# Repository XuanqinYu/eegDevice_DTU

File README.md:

# eegDevice_DTU

Codes contains Python script to use, and codes in Arduino or ESP-IDF for developing.

Design files contains schematic design and PCB design in KiCAD. And the simulation circuit is done in Ti-Tina.

Manual introduces how to use the script to visualize data and develop the device.

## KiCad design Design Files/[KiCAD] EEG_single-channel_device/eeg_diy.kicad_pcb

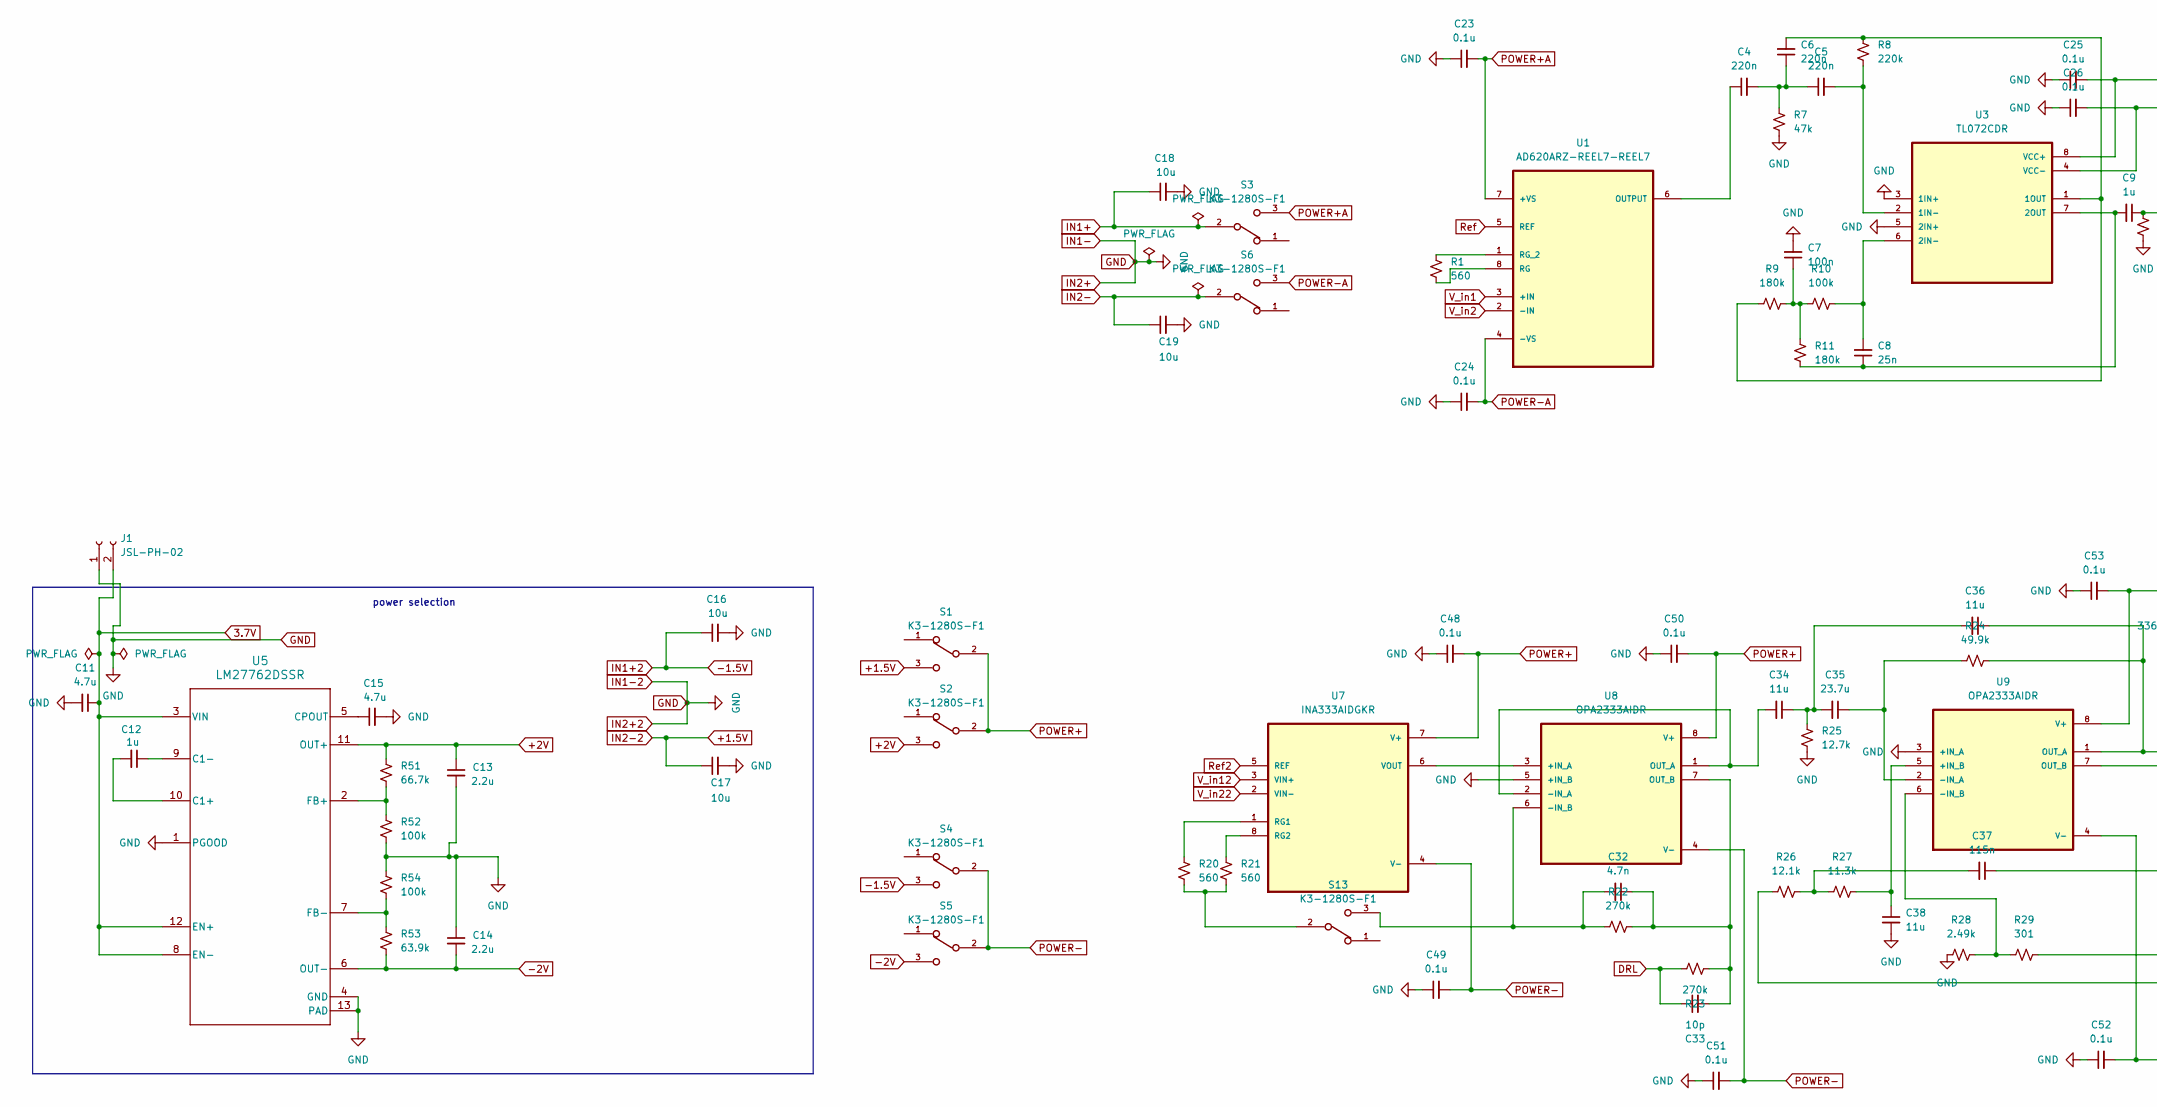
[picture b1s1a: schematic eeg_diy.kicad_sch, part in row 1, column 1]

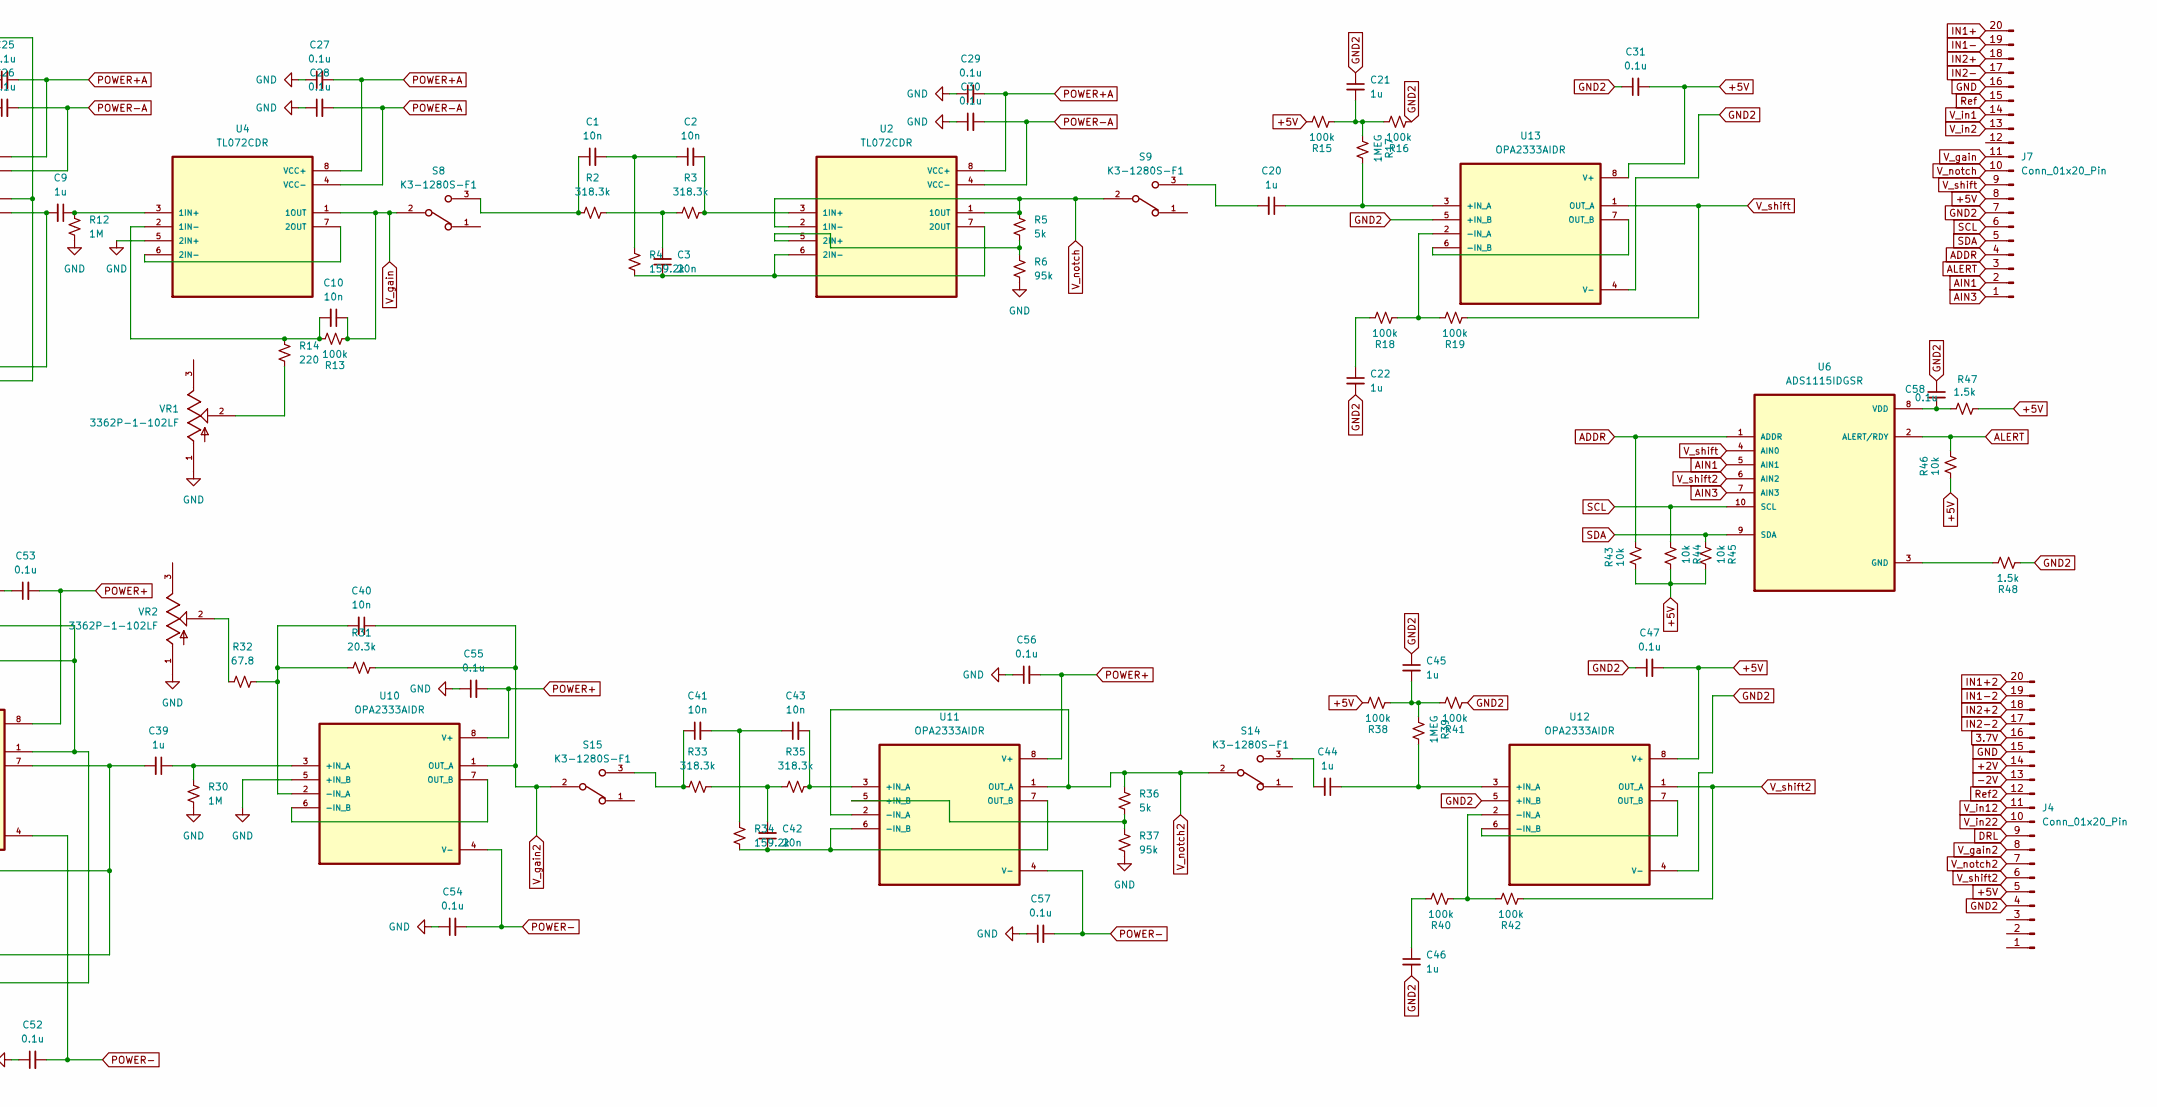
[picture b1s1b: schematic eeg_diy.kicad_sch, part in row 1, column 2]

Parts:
C1, C2, C10, C40, C41, C43: 10n; C_0805_2012Metric
C3, C42: 20n; C_0805_2012Metric
C4, C5, C6: 220n; C_0805_2012Metric
C7: 100n; C_0805_2012Metric
C8: 25n; C_0805_2012Metric
C9, C12, C20, C21, C22, C39, C44, C45, C46: 1u; C_0805_2012Metric
C11, C15: 4.7u; C_0805_2012Metric
C13, C14: 2.2u; C_0603_1608Metric
C16, C17, C18, C19: 10u; C_0805_2012Metric
C23, C24, C25, C26, C27, C28, C29, C30, C31, C47, C48, C49, C50, C51, C52, C53, C54, C55, C56, C57, C58: 0.1u; C_0805_2012Metric
C32: 4.7n; C_0805_2012Metric
C33: 10p; C_0603_1608Metric
C34, C36, C38: 11u; C_0805_2012Metric
C35: 23.7u; C_0805_2012Metric
C37: 115n; C_0805_2012Metric
J1: JSL-PH-02; JST_PH_B2B-PH-K_1x02_P2.00mm_Vertical
J4, J7: Conn_01x20_Pin; PinSocket_1x20_P2.54mm_Vertical
R1, R20, R21: 560; R_0805_2012Metric
R2, R3, R33, R35: 318.3k; R_0603_1608Metric
R4, R34: 159.2k; R_0603_1608Metric
R5, R36: 5k; R_0603_1608Metric
R6, R37: 95k; R_0402_1005Metric
R7: 47k; R_0805_2012Metric
R8: 220k; R_0805_2012Metric
R9, R11: 180k; R_0805_2012Metric
R10, R13, R15, R16, R18, R19, R38, R40, R41, R42, R52, R54: 100k; R_0603_1608Metric
R12, R30: 1M; R_0805_2012Metric
R14: 220; R_0805_2012Metric
R17, R39: 1MEG; R_0805_2012Metric
R22, R23: 270k; R_0805_2012Metric
R24: 49.9k; R_0805_2012Metric
R25: 12.7k; R_0805_2012Metric
R26: 12.1k; R_0805_2012Metric
R27: 11.3k; R_0805_2012Metric
R28: 2.49k; R_0805_2012Metric
R29: 301; R_0805_2012Metric
R31: 20.3k; R_0805_2012Metric
R32: 67.8; R_0805_2012Metric
R43, R44, R45, R46: 10k; R_0805_2012Metric
R47, R48: 1.5k; R_0805_2012Metric
R51: 66.7k; R_0805_2012Metric
R53: 63.9k; R_0603_1608Metric
S1, S2, S3, S4, S5, S6, S8, S9, S13, S14, S15: K3-1280S-F1; SW_JS102011SAQN
U1: AD620ARZ-REEL7-REEL7; SOIC127P599X175-8N; MPN AD620ARZ-REEL7-REEL7
U2, U3, U4: TL072CDR; SOIC127P599X175-8N
U5: LM27762DSSR; DSS0012B
U6: ADS1115IDGSR; SOP50P490X110-10N
U7: INA333AIDGKR; SOP65P490X110-8N
U8, U9, U10, U11, U12, U13: OPA2333AIDR; SOIC127P599X175-8N
VR1, VR2: 3362P-1-102LF; TRIM_3362P-1-102LF; PARTREV 08/26/10

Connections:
3.7V: C11.1, J1.2, J4.16, U5.3 (VIN), U5.8 (EN-), U5.12 (EN+)
+1.5V: C17.1, J4.17, S1.3
+2V: C13.1, J4.14, R51.2, S2.3, U5.11 (OUT+)
+5V: C31.2, C47.2, J4.5, J7.8, R15.1, R38.1, R43.2, R44.1, R45.1, R46.2, R47.2, U12.8 (V+), U13.8 (V+)
-1.5V: C16.1, J4.20, S4.3
-2V: C14.2, J4.13, R53.1, S5.3, U5.6 (OUT-)
ADDR: J7.4, R43.1, U6.1 (ADDR)
AIN1: J7.2, U6.5 (AIN1)
AIN3: J7.1, U6.7 (AIN3)
ALERT: J7.3, R46.1, U6.2 (ALERT/RDY)
DRL: C33.1, J4.9, R23.2
GND: C7.2, C11.2, C13.2, C14.1, C15.2, C16.2, C17.2, C18.2, C19.2, C23.1, C24.1, C25.1, C26.1, C27.1, C28.1, C29.1, C30.1, C38.2, C48.1, C49.1, C50.1, C51.1, C52.1, C53.1, C54.1, C55.1, C56.1, C57.1, J1.1, J4.15, J4.18, J4.19, J7.16, J7.18, J7.19, R6.1, R7.1, R12.2, R25.1, R28.2, R30.2, R37.1, R52.1, R54.2, U3.3 (1IN+), U3.5 (2IN+), U4.5 (2IN+), U5.1 (PGOOD), U5.4 (GND), U5.13 (PAD), U8.5 (+IN_B), U9.3 (+IN_A), U10.5 (+IN_B), VR1.1, VR2.1
GND2: C21.1, C22.2, C31.1, C45.1, C46.2, C47.1, C58.1, J4.4, J7.7, R16.2, R41.2, R48.2, U12.4 (V-), U12.5 (+IN_B), U13.4 (V-), U13.5 (+IN_B)
IN1+: C18.1, J7.20, S3.2
IN2-: C19.1, J7.17, S6.2
unnamed: C1.1, R2.1, S8.3
unnamed: C1.2, C2.1, R4.2
unnamed: C3.2, R2.2, R3.1
unnamed: C4.2, C5.1, C6.1, R7.2
unnamed: C7.1, R9.1, R10.2, R11.1
unnamed: C20.2, S9.3
unnamed: C21.2, R15.2, R16.1, R17.2
unnamed: C22.1, R18.1
unnamed: C34.1, C35.2, C36.2, R25.2
unnamed: C37.2, R26.1, R27.2
unnamed: C41.1, R33.1, S15.3
unnamed: C41.2, C43.1, R34.2
unnamed: C42.2, R33.2, R35.1
unnamed: C44.2, S14.3
unnamed: C45.2, R38.2, R39.2, R41.1
unnamed: C46.1, R40.1
unnamed: R14.2, VR1.2
unnamed: R20.2, R21.2, S13.2
unnamed: R32.1, VR2.2
unnamed: C4.1, U1.6 (OUTPUT)
unnamed: R1.2, U1.8 (RG)
unnamed: R1.1, U1.1 (RG_2)
unnamed: C2.2, R3.2, U2.3 (1IN+)
unnamed: R5.1, R6.2, U2.5 (2IN+)
unnamed: C3.1, R4.1, U2.6 (2IN-), U2.7 (2OUT)
unnamed: C5.2, R8.1, U3.2 (1IN-)
unnamed: C6.2, R8.2, R9.2, U3.1 (1OUT)
unnamed: C8.2, R10.1, U3.6 (2IN-)
unnamed: C8.1, C9.2, R11.2, U3.7 (2OUT)
unnamed: C9.1, R12.1, U4.3 (1IN+)
unnamed: C10.2, R13.1, R14.1, U4.2 (1IN-)
unnamed: U4.6 (2IN-), U4.7 (2OUT)
unnamed: C12.2, U5.10 (C1+)
unnamed: C12.1, U5.9 (C1-)
unnamed: C15.1, U5.5 (CPOUT)
unnamed: R51.1, R52.2, U5.2 (FB+)
unnamed: R53.2, R54.1, U5.7 (FB-)
unnamed: R48.1, U6.3 (GND)
unnamed: C58.2, R47.1, U6.8 (VDD)
unnamed: R20.1, U7.1 (RG1)
unnamed: R21.1, U7.8 (RG2)
unnamed: U7.6 (VOUT), U8.3 (+IN_A)
unnamed: C34.2, U8.1 (OUT_A), U8.2 (-IN_A)
unnamed: C32.2, R22.1, S13.3, U8.6 (-IN_B)
unnamed: C32.1, C33.2, R22.2, R23.1, U8.7 (OUT_B)
unnamed: C38.1, R27.1, U9.5 (+IN_B)
unnamed: C35.1, R24.1, U9.2 (-IN_A)
unnamed: R28.1, R29.2, U9.6 (-IN_B)
unnamed: C36.1, R24.2, R26.2, U9.1 (OUT_A)
unnamed: C37.1, C39.2, R29.1, U9.7 (OUT_B)
unnamed: C39.1, R30.1, U10.3 (+IN_A)
unnamed: C40.2, R31.1, R32.2, U10.2 (-IN_A)
unnamed: U10.6 (-IN_B), U10.7 (OUT_B)
unnamed: C43.2, R35.2, U11.3 (+IN_A)
unnamed: R36.1, R37.2, U11.5 (+IN_B)
unnamed: C42.1, R34.1, U11.6 (-IN_B), U11.7 (OUT_B)
unnamed: C44.1, R39.1, U12.3 (+IN_A)
unnamed: R40.2, R42.1, U12.2 (-IN_A)
unnamed: U12.6 (-IN_B), U12.7 (OUT_B)
unnamed: C20.1, R17.1, U13.3 (+IN_A)
unnamed: R18.2, R19.1, U13.2 (-IN_A)
unnamed: U13.6 (-IN_B), U13.7 (OUT_B)
POWER+: C48.2, C50.2, C53.2, C55.2, C56.2, S1.2, S2.2, U7.7 (V+), U8.8 (V+), U9.8 (V+), U10.8 (V+), U11.8 (V+)
POWER+A: C23.2, C25.2, C27.2, C29.2, S3.3, U1.7 (+VS), U2.8 (VCC+), U3.8 (VCC+), U4.8 (VCC+)
POWER-: C49.2, C51.2, C52.2, C54.2, C57.2, S4.2, S5.2, U7.4 (V-), U8.4 (V-), U9.4 (V-), U10.4 (V-), U11.4 (V-)
POWER-A: C24.2, C26.2, C28.2, C30.2, S6.3, U1.4 (-VS), U2.4 (VCC-), U3.4 (VCC-), U4.4 (VCC-)
Ref: J7.15, U1.5 (REF)
Ref2: J4.12, U7.5 (REF)
SCL: J7.6, R44.2, U6.10 (SCL)
SDA: J7.5, R45.2, U6.9 (SDA)
V_gain: C10.1, J7.11, R13.2, S8.2, U4.1 (1OUT)
V_gain2: C40.1, J4.8, R31.2, S15.2, U10.1 (OUT_A)
V_in1: J7.14, U1.3 (+IN)
V_in2: J7.13, U1.2 (-IN)
V_in12: J4.11, U7.3 (VIN+)
V_in22: J4.10, U7.2 (VIN-)
V_notch: J7.10, R5.2, S9.2, U2.1 (1OUT), U2.2 (1IN-)
V_notch2: J4.7, R36.2, S14.2, U11.1 (OUT_A), U11.2 (-IN_A)
V_shift: J7.9, R19.2, U6.4 (AIN0), U13.1 (OUT_A)
V_shift2: J4.6, R42.2, U6.6 (AIN2), U12.1 (OUT_A)

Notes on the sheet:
power selection

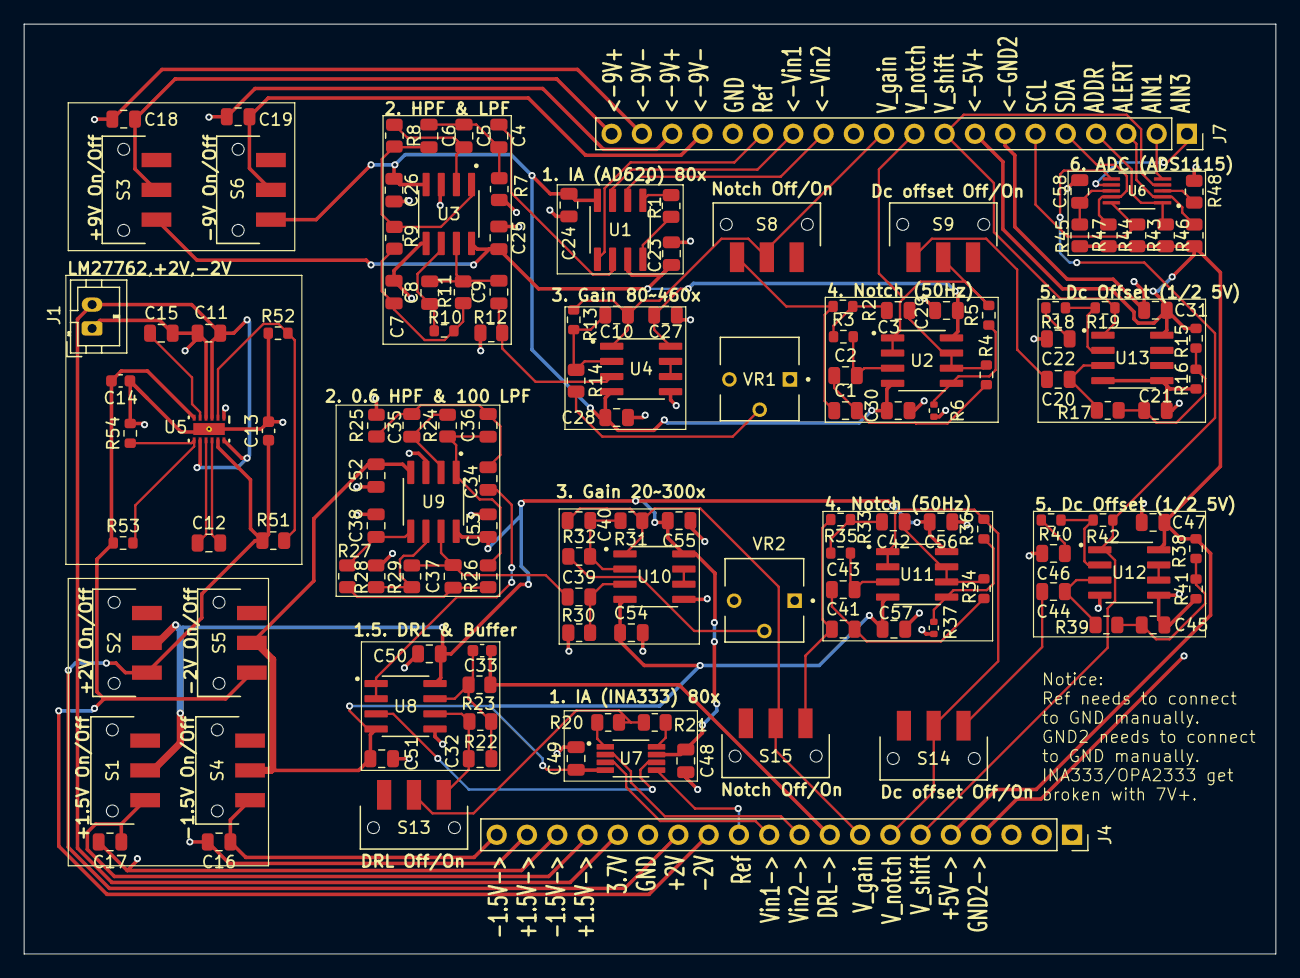
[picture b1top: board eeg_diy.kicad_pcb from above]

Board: 2 copper layers, 105.0 x 78.0 mm, 139 parts (0 on the bottom side), 95 nets.

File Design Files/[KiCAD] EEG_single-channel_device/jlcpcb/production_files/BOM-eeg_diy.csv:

Comment,Designator,Footprint,LCSC,Quantity
JSL-PH-02,J1,JST_PH_B2B-PH-K_1x02_P2.00mm_Vertical,C131337,1
10u,"C16,C17,C18,C19,C34,C36,C38",C_0805_2012Metric,C15850,7
10p,C33,C_0603_1608Metric,C1634,1
5k,"R36,R5",R_0603_1608Metric,C166926,2
10n,"C1,C10,C2,C40,C41,C43",C_0805_2012Metric,C1710,6
20n,"C3,C42",C_0805_2012Metric,C1726,2
25n,C8,C_0805_2012Metric,C1734,1
10k,"R43,R44,R45,R46",R_0805_2012Metric,C17414,4
11.3k,R27,R_0805_2012Metric,C17416,1
4.7n,C32,C_0805_2012Metric,C1744,1
12.1k,R26,R_0805_2012Metric,C17444,1
12.7k,R25,R_0805_2012Metric,C17455,1
180k,"R11,R9",R_0805_2012Metric,C17501,2
1M,"R12,R17,R30,R39",R_0805_2012Metric,C17514,4
220k,R8,R_0805_2012Metric,C17556,1
220,R14,R_0805_2012Metric,C17557,1
270k,"R22,R23",R_0805_2012Metric,C17589,2
301,R29,R_0805_2012Metric,C17617,1
47k,R7,R_0805_2012Metric,C17713,1
49.9k,R24,R_0805_2012Metric,C17719,1
4.7u,"C11,C15",C_0805_2012Metric,C1779,2
66.7k,R51,R_0805_2012Metric,C17801,1
67.8,R32,R_0805_2012Metric,C17802,1
INA333AIDGKR,U7,SOP65P490X110-8N,C19450,1
318.3k,"R2,R3,R33,R35",R_0603_1608Metric,C20165692,4
2.49k,R28,R_0805_2012Metric,C21237,1
95k,"R37,R6",R_0402_1005Metric,C22375098,2
159.2k,"R34,R4",R_0603_1608Metric,C22813,2
2.2u,"C13,C14",C_0603_1608Metric,C23630,2
100k,"R10,R13,R15,R16,R18,R19,R38,R40,R41,R42,R52,R54",R_0603_1608Metric,C25803,12
0.1u,"C23,C24,C25,C26,C27,C28,C29,C30,C31,C37,C47,C48,C49,C50,C51,C52,C53,C54,C55,C56,C57,C58,C7",C_0805_2012Metric,C28233,23
1u,"C12,C20,C21,C22,C39,C44,C45,C46,C9",C_0805_2012Metric,C28323,9
560,"R1,R20,R21",R_0805_2012Metric,C28636,3
63.9k,R53,R_0603_1608Metric,C2902643,1
ADS1115IDGSR,U6,SOP50P490X110-10N,C37593,1
OPA2333AIDR,"U10,U11,U12,U13,U8,U9",SOIC127P599X175-8N,C38732,6
1.5k,"R47,R48",R_0805_2012Metric,C4310,2
20.3k,R31,R_0805_2012Metric,C4328,1
23.7u,C35,C_0805_2012Metric,C45783,1
LM27762DSSR,U5,DSS0012B,C473398,1
Conn_01x20_Pin,"J4,J7",PinSocket_1x20_P2.54mm_Vertical,C50981,2
220n,"C4,C5,C6",C_0805_2012Metric,C5378,3
3362P-1-102LF,"VR1,VR2",TRIM_3362P-1-102LF,C58161,2
TL072CDR,"U2,U3,U4",SOIC127P599X175-8N,C67473,3
K3-1280S-F1,"S1,S13,S14,S15,S2,S3,S4,S5,S6,S8,S9",SW_JS102011SAQN,C92658,11
AD620ARZ-REEL7-REEL7,U1,SOIC127P599X175-8N,C9675,1

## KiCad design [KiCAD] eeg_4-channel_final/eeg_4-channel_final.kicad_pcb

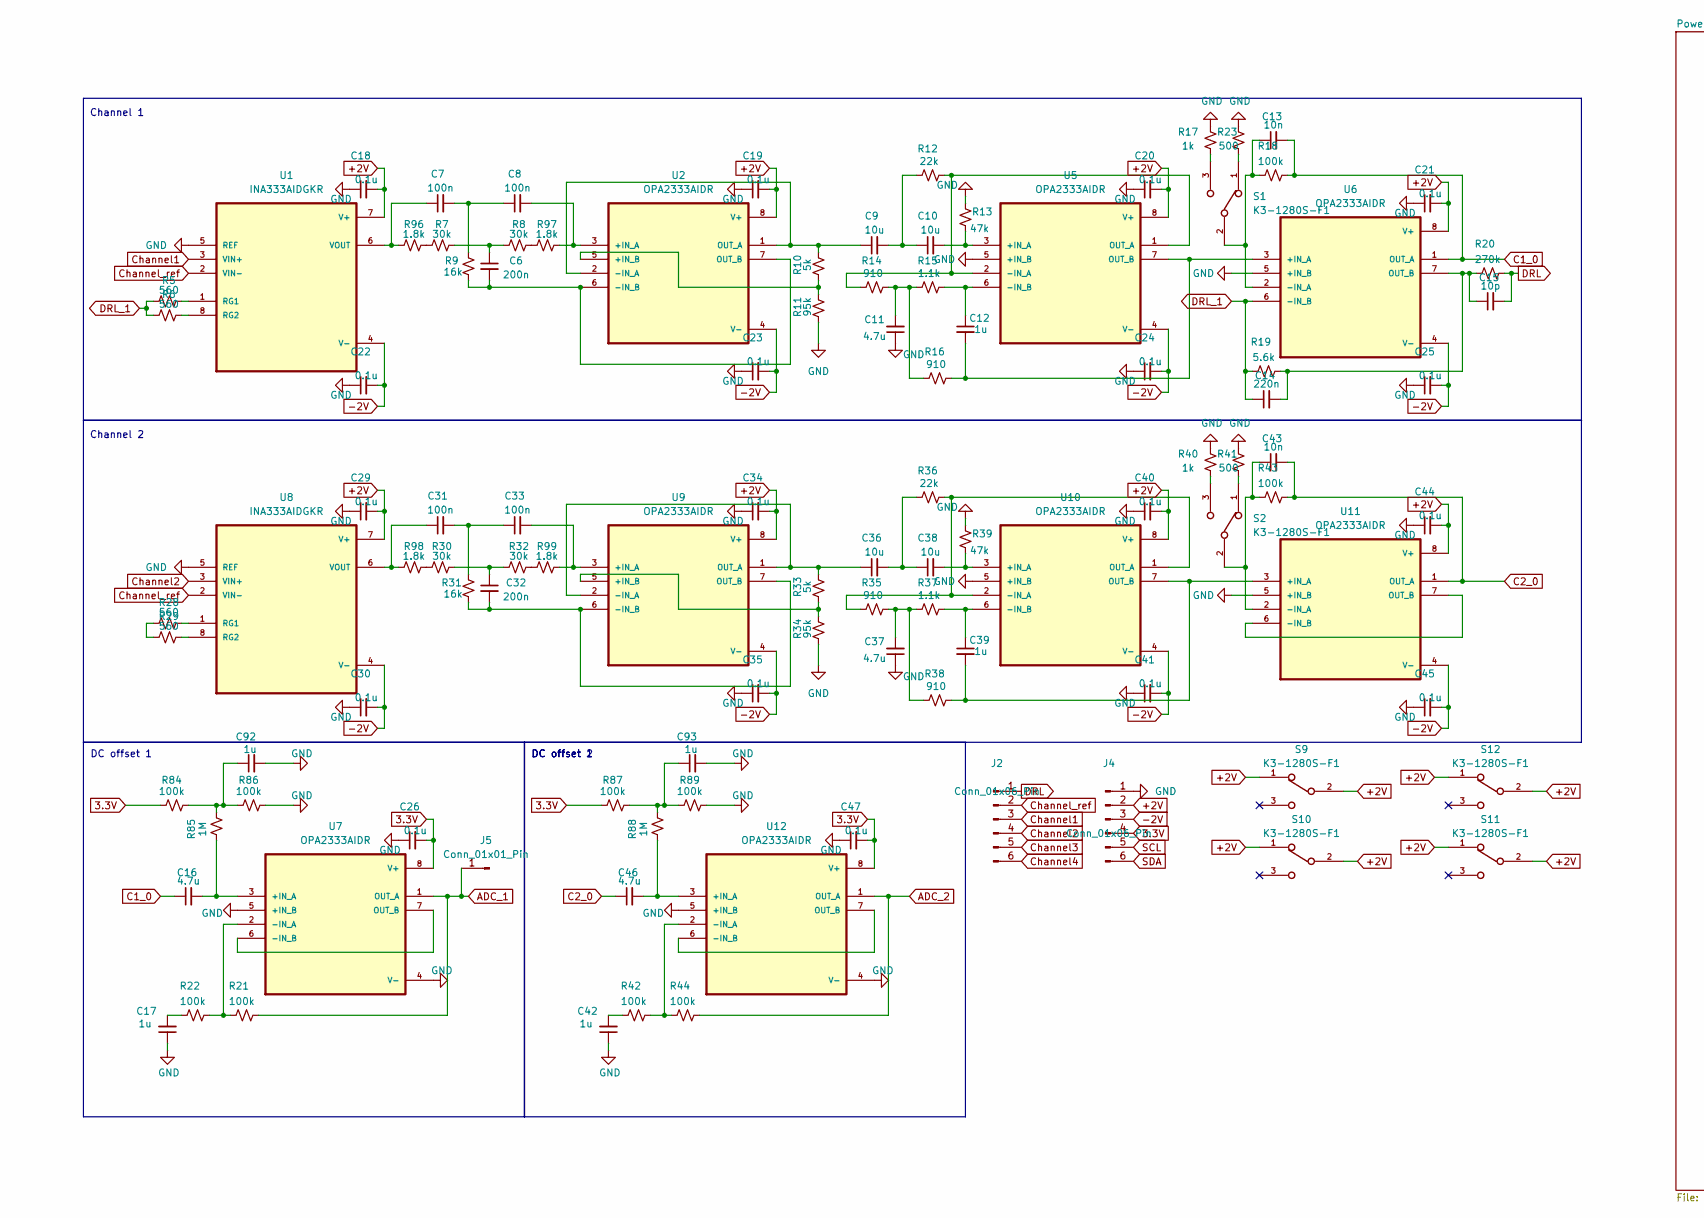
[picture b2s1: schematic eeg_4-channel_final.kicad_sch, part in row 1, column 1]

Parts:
C6, C32: 200n; C_0805_2012Metric
C7, C8, C31, C33: 100n; C_0805_2012Metric
C9, C10, C36, C38: 10u; C_0805_2012Metric
C11, C16, C37, C46: 4.7u; C_0805_2012Metric
C12, C17, C39, C42, C92, C93: 1u; C_0805_2012Metric
C13, C43: 10n; C_0805_2012Metric
C14: 220n; C_0805_2012Metric
C15: 10p; C_0603_1608Metric
C18, C19, C20, C21, C22, C23, C24, C25, C26, C29, C30, C34, C35, C40, C41, C44, C45, C47: 0.1u; C_0805_2012Metric
J2, J4: Conn_01x06_Pin; PinHeader_1x06_P2.54mm_Vertical
J5: Conn_01x01_Pin; PinHeader_1x01_P2.54mm_Vertical
R5, R6, R28, R29: 560; R_0805_2012Metric
R7, R8, R30, R32: 30k; R_0805_2012Metric
R9, R31: 16k; R_0805_2012Metric
R10, R33: 5k; R_0805_2012Metric
R11, R34: 95k; R_0603_1608Metric
R12, R36: 22k; R_0805_2012Metric
R13, R39: 47k; R_0805_2012Metric
R14, R16, R35, R38: 910; R_0805_2012Metric
R15, R37: 1.1k; R_0603_1608Metric
R17, R40: 1k; R_0805_2012Metric
R18, R21, R22, R42, R43, R44, R84, R86, R87, R89: 100k; R_0603_1608Metric
R19: 5.6k; R_0805_2012Metric
R20: 270k; R_0805_2012Metric
R23, R41: 500; R_0805_2012Metric
R85, R88: 1M; R_0805_2012Metric
R96, R97, R98, R99: 1.8k; R_0805_2012Metric
S1, S2, S9, S10, S11, S12: K3-1280S-F1; SW_JS102011SAQN
U1, U8: INA333AIDGKR; SOP65P490X110-8N
U2, U5, U6, U7, U9, U10, U11, U12: OPA2333AIDR; SOIC127P599X175-8N

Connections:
3.3V: C26.2, C47.2, J4.4, R84.1, R87.1, U7.8 (V+), U12.8 (V+); also elsewhere on the board
+2V: C18.2, C19.2, C20.2, C21.2, C29.2, C34.2, C40.2, C44.2, J4.2, S9.1, S9.2, S10.1, S10.2, S11.1, S11.2, S12.1, S12.2, U1.7 (V+), U2.8 (V+), U5.8 (V+), U6.8 (V+), U8.7 (V+), U9.8 (V+), U10.8 (V+), U11.8 (V+); also elsewhere on the board
-2V: C22.2, C23.2, C24.2, C25.2, C30.2, C35.2, C41.2, C45.2, J4.3, U1.4 (V-), U2.4 (V-), U5.4 (V-), U6.4 (V-), U8.4 (V-), U9.4 (V-), U10.4 (V-), U11.4 (V-); also elsewhere on the board
ADC_1: J5.1, R21.2, U7.1 (OUT_A); also elsewhere on the board
ADC_2: R44.2, U12.1 (OUT_A); also elsewhere on the board
C1_0: C13.2, C16.1, R18.2, U6.1 (OUT_A)
C2_0: C43.2, C46.1, R43.2, U11.1 (OUT_A)
Channel1: J2.3, U1.3 (VIN+)
Channel2: J2.4, U8.3 (VIN+)
Channel3: J2.5; also elsewhere on the board
Channel4: J2.6; also elsewhere on the board
Channel_ref: J2.2, U1.2 (VIN-), U8.2 (VIN-); also elsewhere on the board
DRL: C15.2, J2.1, R20.2
DRL_1: C14.1, R5.2, R6.2, R19.1, U6.6 (-IN_B)
GND: C11.1, C17.1, C18.1, C19.1, C20.1, C21.1, C22.1, C23.1, C24.1, C25.1, C26.1, C29.1, C30.1, C34.1, C35.1, C37.1, C40.1, C41.1, C42.1, C44.1, C45.1, C47.1, C92.2, C93.2, J4.1, R11.2, R13.1, R17.1, R23.2, R34.2, R39.1, R40.1, R41.2, R86.2, R89.2, U1.5 (REF), U5.5 (+IN_B), U6.5 (+IN_B), U7.4 (V-), U7.5 (+IN_B), U8.5 (REF), U10.5 (+IN_B), U11.5 (+IN_B), U12.4 (V-), U12.5 (+IN_B); also elsewhere on the board
unnamed: C6.1, R7.1, R8.2
unnamed: C7.2, C8.1, R9.1
unnamed: C9.2, C10.1, R12.1
unnamed: C11.2, R14.2, R15.1, R16.1
unnamed: C17.2, R22.1
unnamed: C31.2, C33.1, R31.1
unnamed: C32.1, R30.1, R32.2
unnamed: C36.2, C38.1, R36.1
unnamed: C37.2, R35.2, R37.1, R38.1
unnamed: C42.2, R42.1
unnamed: C92.1, R84.2, R85.2, R86.1
unnamed: C93.1, R87.2, R88.2, R89.1
unnamed: R7.2, R96.1
unnamed: R8.1, R97.2
unnamed: R17.2, S1.3
unnamed: R23.1, S1.1
unnamed: R28.2, R29.2
unnamed: R30.2, R98.1
unnamed: R32.1, R99.2
unnamed: R40.2, S2.3
unnamed: R41.1, S2.1
unnamed: R5.1, U1.1 (RG1)
unnamed: R6.1, U1.8 (RG2)
unnamed: C7.1, R96.2, U1.6 (VOUT)
unnamed: C8.2, R97.1, U2.3 (+IN_A)
unnamed: R10.2, R11.1, U2.5 (+IN_B)
unnamed: C9.1, R10.1, U2.1 (OUT_A), U2.2 (-IN_A)
unnamed: C6.2, R9.2, U2.6 (-IN_B), U2.7 (OUT_B)
unnamed: C10.2, R13.2, U5.3 (+IN_A)
unnamed: R12.2, R14.1, U5.1 (OUT_A), U5.2 (-IN_A)
unnamed: C12.1, R15.2, U5.6 (-IN_B)
unnamed: C12.2, R16.2, U5.7 (OUT_B), U6.3 (+IN_A)
unnamed: C13.1, R18.1, S1.2, U6.2 (-IN_A)
unnamed: C14.2, C15.1, R19.2, R20.1, U6.7 (OUT_B)
unnamed: C16.2, R85.1, U7.3 (+IN_A)
unnamed: R21.1, R22.2, U7.2 (-IN_A)
unnamed: U7.6 (-IN_B), U7.7 (OUT_B)
unnamed: R28.1, U8.1 (RG1)
unnamed: R29.1, U8.8 (RG2)
unnamed: C31.1, R98.2, U8.6 (VOUT)
unnamed: C33.2, R99.1, U9.3 (+IN_A)
unnamed: R33.2, R34.1, U9.5 (+IN_B)
unnamed: C36.1, R33.1, U9.1 (OUT_A), U9.2 (-IN_A)
unnamed: C32.2, R31.2, U9.6 (-IN_B), U9.7 (OUT_B)
unnamed: C38.2, R39.2, U10.3 (+IN_A)
unnamed: R35.1, R36.2, U10.1 (OUT_A), U10.2 (-IN_A)
unnamed: C39.1, R37.2, U10.6 (-IN_B)
unnamed: C39.2, R38.2, U10.7 (OUT_B), U11.3 (+IN_A)
unnamed: C43.1, R43.1, S2.2, U11.2 (-IN_A)
unnamed: U11.6 (-IN_B), U11.7 (OUT_B)
unnamed: C46.2, R88.1, U12.3 (+IN_A)
unnamed: R42.2, R44.1, U12.2 (-IN_A)
unnamed: U12.6 (-IN_B), U12.7 (OUT_B)
SCL: J4.5; also elsewhere on the board
SDA: J4.6; also elsewhere on the board

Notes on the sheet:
Channel 1
DC offset 2
DC offset 1
Channel 2

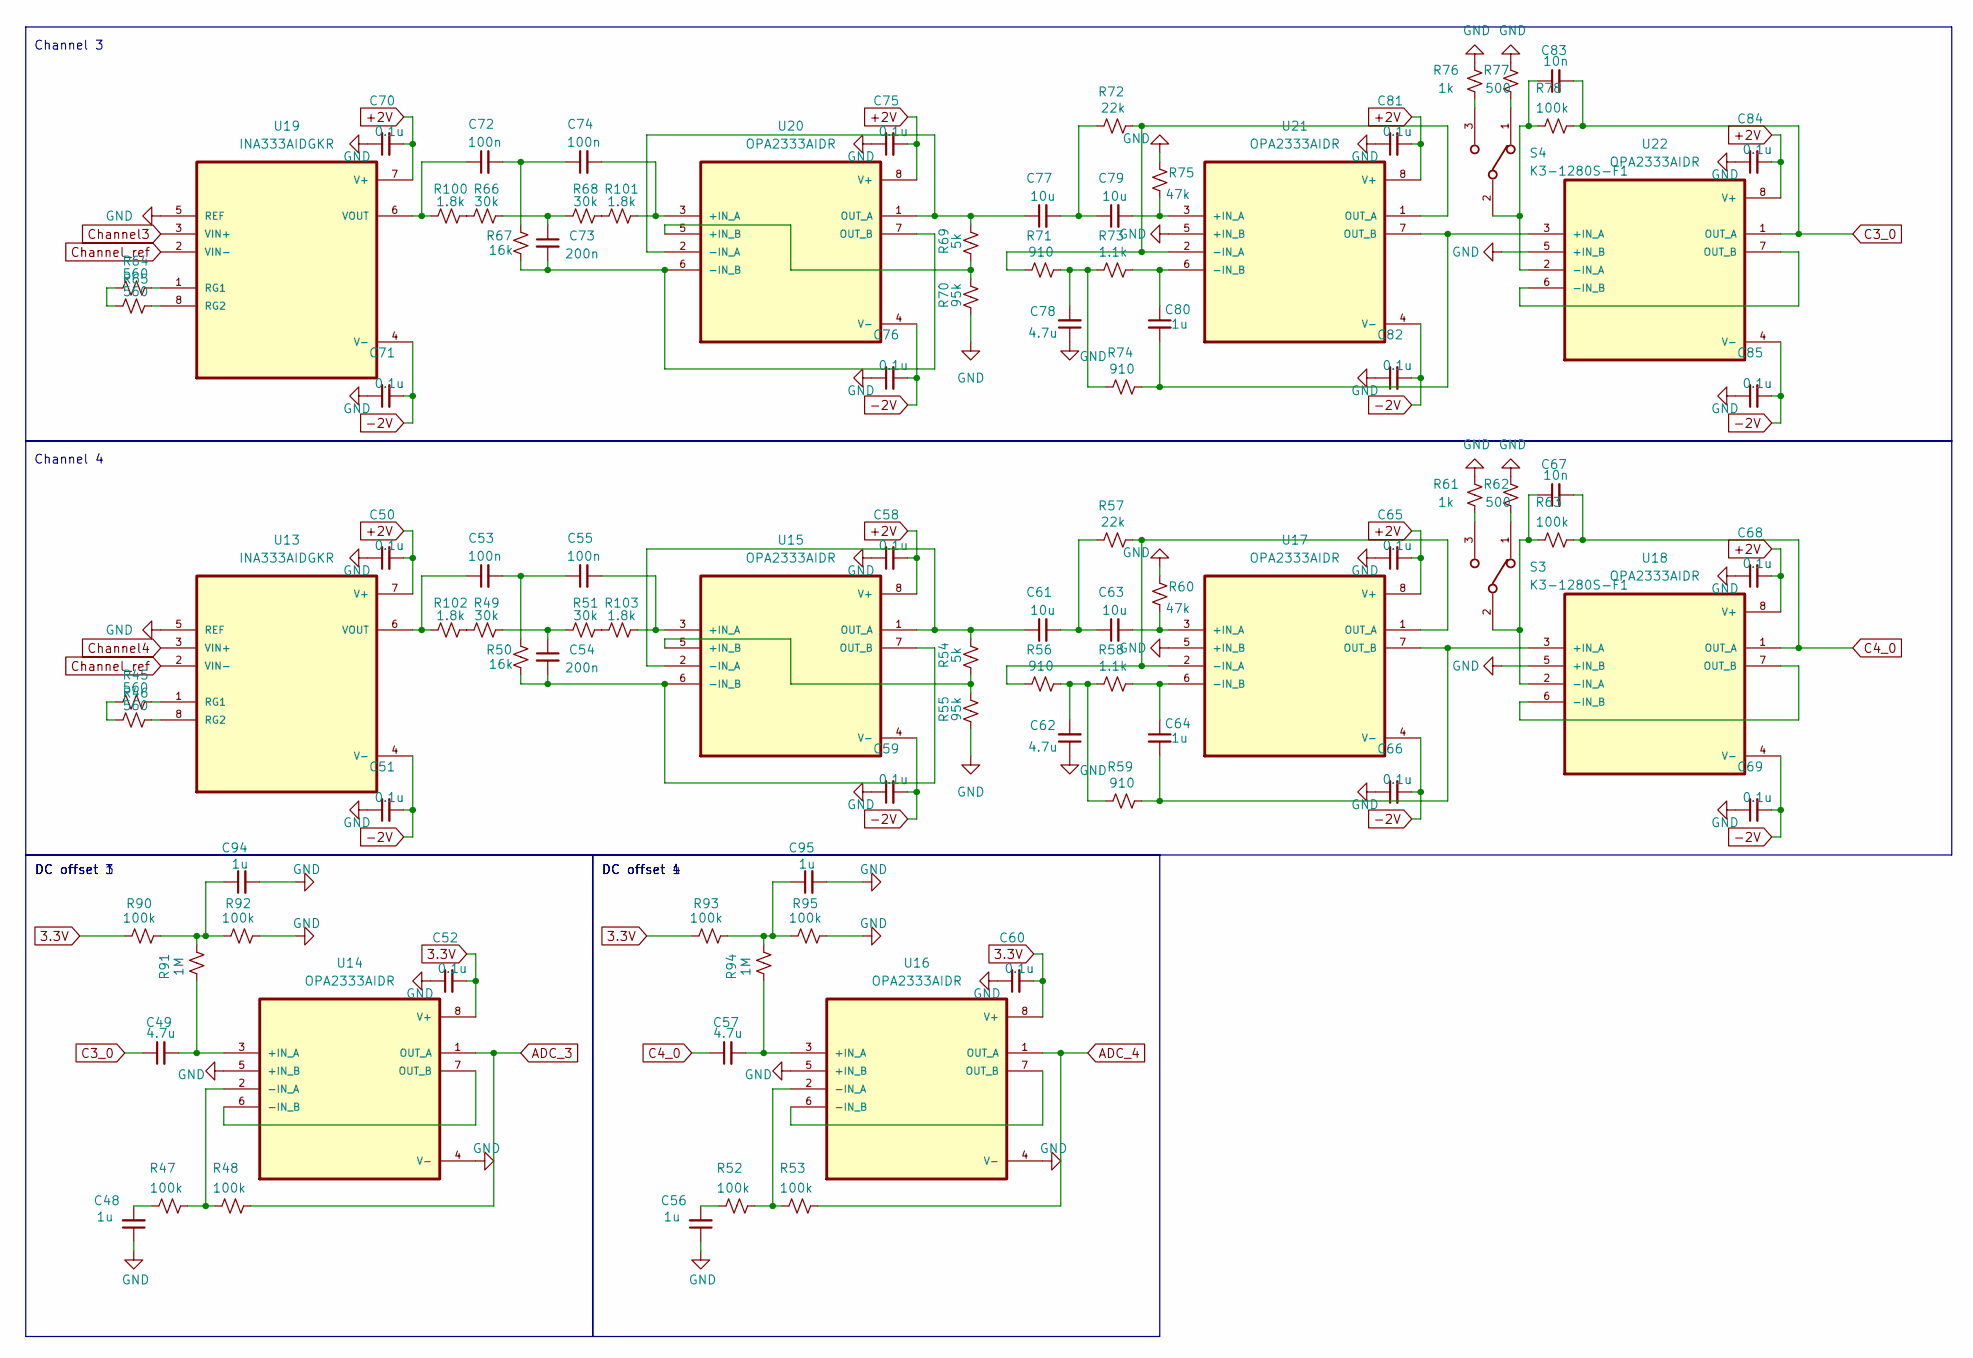
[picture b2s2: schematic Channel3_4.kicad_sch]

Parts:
C48, C56, C64, C80, C94, C95: 1u; C_0805_2012Metric
C49, C57, C62, C78: 4.7u; C_0805_2012Metric
C50, C51, C52, C58, C59, C60, C65, C66, C68, C69, C70, C71, C75, C76, C81, C82, C84, C85: 0.1u; C_0805_2012Metric
C53, C55, C72, C74: 100n; C_0805_2012Metric
C54, C73: 200n; C_0805_2012Metric
C61, C63, C77, C79: 10u; C_0805_2012Metric
C67, C83: 10n; C_0805_2012Metric
R45, R46, R64, R65: 560; R_0805_2012Metric
R47, R48, R52, R53, R63, R78, R90, R92, R93, R95: 100k; R_0603_1608Metric
R49, R51, R66, R68: 30k; R_0805_2012Metric
R50, R67: 16k; R_0805_2012Metric
R54, R69: 5k; R_0805_2012Metric
R55, R70: 95k; R_0603_1608Metric
R56, R59, R71, R74: 910; R_0805_2012Metric
R57, R72: 22k; R_0805_2012Metric
R58, R73: 1.1k; R_0603_1608Metric
R60, R75: 47k; R_0805_2012Metric
R61, R76: 1k; R_0805_2012Metric
R62, R77: 500; R_0805_2012Metric
R91, R94: 1M; R_0805_2012Metric
R100, R101, R102, R103: 1.8k; R_0805_2012Metric
S3, S4: K3-1280S-F1; SW_JS102011SAQN
U13, U19: INA333AIDGKR; SOP65P490X110-8N
U14, U15, U16, U17, U18, U20, U21, U22: OPA2333AIDR; SOIC127P599X175-8N

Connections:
3.3V: C52.2, C60.2, R90.1, R93.1, U14.8 (V+), U16.8 (V+); also elsewhere on the board
+2V: C50.2, C58.2, C65.2, C68.2, C70.2, C75.2, C81.2, C84.2, U13.7 (V+), U15.8 (V+), U17.8 (V+), U18.8 (V+), U19.7 (V+), U20.8 (V+), U21.8 (V+), U22.8 (V+); also elsewhere on the board
-2V: C51.2, C59.2, C66.2, C69.2, C71.2, C76.2, C82.2, C85.2, U13.4 (V-), U15.4 (V-), U17.4 (V-), U18.4 (V-), U19.4 (V-), U20.4 (V-), U21.4 (V-), U22.4 (V-); also elsewhere on the board
ADC_3: R48.2, U14.1 (OUT_A); also elsewhere on the board
ADC_4: R53.2, U16.1 (OUT_A); also elsewhere on the board
C3_0: C49.1, C83.2, R78.2, U22.1 (OUT_A)
C4_0: C57.1, C67.2, R63.2, U18.1 (OUT_A)
Channel3: U19.3 (VIN+); also elsewhere on the board
Channel4: U13.3 (VIN+); also elsewhere on the board
Channel_ref: U13.2 (VIN-), U19.2 (VIN-); also elsewhere on the board
GND: C48.1, C50.1, C51.1, C52.1, C56.1, C58.1, C59.1, C60.1, C62.1, C65.1, C66.1, C68.1, C69.1, C70.1, C71.1, C75.1, C76.1, C78.1, C81.1, C82.1, C84.1, C85.1, C94.2, C95.2, R55.2, R60.1, R61.1, R62.2, R70.2, R75.1, R76.1, R77.2, R92.2, R95.2, U13.5 (REF), U14.4 (V-), U14.5 (+IN_B), U16.4 (V-), U16.5 (+IN_B), U17.5 (+IN_B), U18.5 (+IN_B), U19.5 (REF), U21.5 (+IN_B), U22.5 (+IN_B); also elsewhere on the board
unnamed: C48.2, R47.1
unnamed: C53.2, C55.1, R50.1
unnamed: C54.1, R49.1, R51.2
unnamed: C56.2, R52.1
unnamed: C61.2, C63.1, R57.1
unnamed: C62.2, R56.2, R58.1, R59.1
unnamed: C72.2, C74.1, R67.1
unnamed: C73.1, R66.1, R68.2
unnamed: C77.2, C79.1, R72.1
unnamed: C78.2, R71.2, R73.1, R74.1
unnamed: C94.1, R90.2, R91.2, R92.1
unnamed: C95.1, R93.2, R94.2, R95.1
unnamed: R45.2, R46.2
unnamed: R61.2, S3.3
unnamed: R62.1, S3.1
unnamed: R64.2, R65.2
unnamed: R76.2, S4.3
unnamed: R77.1, S4.1
unnamed: R66.2, R100.1
unnamed: R68.1, R101.2
unnamed: R49.2, R102.1
unnamed: R51.1, R103.2
unnamed: R45.1, U13.1 (RG1)
unnamed: R46.1, U13.8 (RG2)
unnamed: C53.1, R102.2, U13.6 (VOUT)
unnamed: C49.2, R91.1, U14.3 (+IN_A)
unnamed: R47.2, R48.1, U14.2 (-IN_A)
unnamed: U14.6 (-IN_B), U14.7 (OUT_B)
unnamed: C55.2, R103.1, U15.3 (+IN_A)
unnamed: R54.2, R55.1, U15.5 (+IN_B)
unnamed: C61.1, R54.1, U15.1 (OUT_A), U15.2 (-IN_A)
unnamed: C54.2, R50.2, U15.6 (-IN_B), U15.7 (OUT_B)
unnamed: C57.2, R94.1, U16.3 (+IN_A)
unnamed: R52.2, R53.1, U16.2 (-IN_A)
unnamed: U16.6 (-IN_B), U16.7 (OUT_B)
unnamed: C63.2, R60.2, U17.3 (+IN_A)
unnamed: R56.1, R57.2, U17.1 (OUT_A), U17.2 (-IN_A)
unnamed: C64.1, R58.2, U17.6 (-IN_B)
unnamed: C64.2, R59.2, U17.7 (OUT_B), U18.3 (+IN_A)
unnamed: C67.1, R63.1, S3.2, U18.2 (-IN_A)
unnamed: U18.6 (-IN_B), U18.7 (OUT_B)
unnamed: R64.1, U19.1 (RG1)
unnamed: R65.1, U19.8 (RG2)
unnamed: C72.1, R100.2, U19.6 (VOUT)
unnamed: C74.2, R101.1, U20.3 (+IN_A)
unnamed: R69.2, R70.1, U20.5 (+IN_B)
unnamed: C77.1, R69.1, U20.1 (OUT_A), U20.2 (-IN_A)
unnamed: C73.2, R67.2, U20.6 (-IN_B), U20.7 (OUT_B)
unnamed: C79.2, R75.2, U21.3 (+IN_A)
unnamed: R71.1, R72.2, U21.1 (OUT_A), U21.2 (-IN_A)
unnamed: C80.1, R73.2, U21.6 (-IN_B)
unnamed: C80.2, R74.2, U21.7 (OUT_B), U22.3 (+IN_A)
unnamed: C83.1, R78.1, S4.2, U22.2 (-IN_A)
unnamed: U22.6 (-IN_B), U22.7 (OUT_B)

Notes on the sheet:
DC offset 3
DC offset 4
DC offset 1
Channel 3
Channel 4
